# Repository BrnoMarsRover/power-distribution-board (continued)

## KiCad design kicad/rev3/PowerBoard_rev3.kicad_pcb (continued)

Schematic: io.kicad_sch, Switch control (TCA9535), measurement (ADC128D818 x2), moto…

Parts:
C112, C113, C114, C115, C116, C118, C120: 100nF; C_0603_1608Metric_Pad1.08x0.95mm_HandSolder; MPN C0603C104K5RACTU
C117, C119: 1uF/16V; C_0603_1608Metric_Pad1.08x0.95mm_HandSolder; MPN C0603C105K3RACTU
D21: 1N5819HW; D_SOD-123; MPN 1N5819HW-7-F
J36: B2B-XH-A(LF)(SN) (motor switch); JST_XH_B2B-XH-A_1x02_P2.50mm_Vertical; MPN B2B-XH-A(LF)(SN)
J37: B4B-XH-A(LF)(SN) (power button, 2-pole); JST_XH_B4B-XH-A_1x04_P2.50mm_Vertical; MPN B4B-XH-A(LF)(SN)
J38: B2B-XH-A(LF)(SN) (BMS soft-start via E-STOP); JST_XH_B2B-XH-A_1x02_P2.50mm_Vertical; MPN B2B-XH-A(LF)(SN)
R165, R173: 100k; R_0603_1608Metric_Pad0.98x0.95mm_HandSolder; MPN RC0603FR-07100KL
R166, R167, R175: 1k; R_0603_1608Metric_Pad0.98x0.95mm_HandSolder; MPN RC0603FR-071KL
R168, R170, R171, R174: 10k; R_0603_1608Metric_Pad0.98x0.95mm_HandSolder; MPN RC0603FR-0710KL
R169: 1M; R_0603_1608Metric_Pad0.98x0.95mm_HandSolder; MPN RC0603FR-071ML
R172: 330; R_0603_1608Metric_Pad0.98x0.95mm_HandSolder; MPN RC0603FR-07330RL
TP43: MOTOR_KILL; TestPoint_Pad_D1.5mm; MPN none: PCB pad
TP44: GND; TestPoint_Keystone_5015_Micro_Mini; MPN 5015
U17: TCA9535PWR; TSSOP-24_4.4x7.8mm_P0.65mm; MPN TCA9535PWR
U18: SN74LVC1G74DCUT; VSSOP-8_2.3x2mm_P0.5mm; MPN SN74LVC1G74DCUT
U19: SN74LVC1G17DBVR; SOT-23-5; MPN SN74LVC1G17DBVR
U20, U21: ADC128D818; TSSOP-16_4.4x5mm_P0.65mm; MPN ADC128D818CIMTX/NOPB
U22: AQY282S; SO-4_4.4x4.3mm_P2.54mm; MPN AQY282S

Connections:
+3V3: C112.1, C113.1, C116.1, C117.1, C118.1, C119.1, R166.1, R171.1, R174.1, U17.24 (VCC), U18.2 (D), U18.7 (~PRE), U18.8 (VCC), U19.5 (VCC), U20.5 (V+), U21.5 (V+); also elsewhere on the board
/Switch control (TCA9535), measurement (ADC128D818 x2), motor/BTN_SNS: J37.3, R174.2, R175.1
/Switch control (TCA9535), measurement (ADC128D818 x2), motor/SS_A: J37.1, J38.1, U22.3
/Switch control (TCA9535), measurement (ADC128D818 x2), motor/SS_B: J37.2, J38.2, U22.4
BOOST_DIS: U17.18 (P15); also elsewhere on the board
GND: C112.2, C113.2, C114.2, C115.2, C116.2, C117.2, C118.2, C119.2, C120.2, J37.4, R165.2, R168.2, R170.2, R173.2, TP44.1, U17.2 (A1), U17.3 (A2), U17.12 (GND), U17.21 (A0), U18.4 (GND), U19.3 (GND), U20.4 (GND), U20.7 (A0), U20.8 (A1), U20.11 (IN5), U21.4 (GND), U21.8 (A1), U21.9 (IN7), U22.2; also elsewhere on the board
I2C_SCL: U17.22 (SCL), U20.3 (SCL), U21.3 (SCL); also elsewhere on the board
I2C_SDA: U17.23 (SDA), U20.2 (SDA), U21.2 (SDA); also elsewhere on the board
IMON_5: U20.12 (IN4); also elsewhere on the board
IMON_12: U20.13 (IN3); also elsewhere on the board
IMON_24: U20.14 (IN2); also elsewhere on the board
IMON_42C: U20.15 (IN1); also elsewhere on the board
IMON_42D: U20.16 (IN0); also elsewhere on the board
INPG_5: U17.15 (P12); also elsewhere on the board
INPG_12: U17.14 (P11); also elsewhere on the board
INPG_24: U17.13 (P10); also elsewhere on the board
INPG_42C: U17.4 (P00); also elsewhere on the board
INPG_42D: U17.10 (P06); also elsewhere on the board
INP_5: U17.8 (P04); also elsewhere on the board
INP_12: U17.7 (P03); also elsewhere on the board
INP_24: U17.6 (P02); also elsewhere on the board
INP_42C: U17.5 (P01); also elsewhere on the board
INP_42D: U17.11 (P07); also elsewhere on the board
MOTOR_KILL: TP43.1, U18.3 (~Q); also elsewhere on the board
MOTOR_OK: C114.1, D21.1 (K), R167.2, R169.1; also elsewhere on the board
unnamed: C115.1, D21.2 (A), R169.2, U19.2
unnamed: J36.1, R166.2
unnamed: J36.2, R167.1, R168.1
unnamed: R172.2, U22.1
unnamed: R165.1, U17.17 (P14), U18.1 (C)
unnamed: U18.6 (~CLR), U19.4
unnamed: R170.1, R171.2, U21.7 (A0)
PWR_BTN: C120.1, R175.2; also elsewhere on the board
PWR_HOLD: R172.1, R173.1; also elsewhere on the board
VSNS_IN_5: U21.10 (IN6); also elsewhere on the board
VSNS_IN_12: U21.11 (IN5); also elsewhere on the board
VSNS_IN_24: U21.12 (IN4); also elsewhere on the board
VSNS_OUT_5: U21.14 (IN2); also elsewhere on the board
VSNS_OUT_12: U21.15 (IN1); also elsewhere on the board
VSNS_OUT_24: U21.16 (IN0); also elsewhere on the board
VSNS_OUT_42C: U20.9 (IN7); also elsewhere on the board
VSNS_OUT_42D: U20.10 (IN6); also elsewhere on the board
VSNS_OUT_54: U21.13 (IN3); also elsewhere on the board

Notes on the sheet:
It stays off after the switch closes until the ESP32 clocks MOTOR_ARM, which it does only after dropping INP and re-running pre-charge. Power-on also starts latched off. The battery E-STOP is separate (BMS soft-start).
TCA9535 at 0x20 holds INP / INP_G for all five switches, so they keep their state across an ESP32 reset.
Rear-panel motor switch (closed = motors allowed): opening it clears the latch (Q low, /Q high) -> MOTOR_KILL holds the drive group off.
ADC128D818 at 0x1D (A1 = A0 = LOW) and 0x1E (A1 = LOW, A0 = MID). Internal 2.56 V reference (VREF pin open); firmware must select mode 1 (reg 0Bh) or IN7 is not converted. 12 ms per channel.
Soft power: the BMS soft-start loop (through the E-STOP) is closed by button pole 1 or by the AQY282S that the ESP32 holds (PWR_HOLD, GPIO40). Pole 2 reads the button (PWR_BTN, GPIO41, low = on). Button off: the ESP32 asks the Jetson to stow and shut down, then releases PWR_HOLD. A reset or a dead 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
Switch control (TCA9535), measurement (ADC128D818 x2), motor-switch latch
The motor-switch RC (1 M x 100 nF hold-off, diode for a fast clear) goes through a Schmitt buffer into /CLR.

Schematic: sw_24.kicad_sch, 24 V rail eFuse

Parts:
C29: 100nF/100V; C_0603_1608Metric_Pad1.08x0.95mm_HandSolder; MPN CL10B104KC8NNNC
C30: 1uF/100V; C_1206_3216Metric_Pad1.33x1.80mm_HandSolder; MPN GRM31CR72A105KA01L
C31: 10uF/50V; C_1210_3225Metric_Pad1.33x2.70mm_HandSolder; MPN CL32B106KBJNNNE
C32: 270nF/50V; C_1206_3216Metric_Pad1.33x1.80mm_HandSolder; MPN C1206C274K5RACTU
C33, C34, C39: 10nF; C_0603_1608Metric_Pad1.08x0.95mm_HandSolder; MPN CL10B103KB8NNNC
C35: 22uF/10V; C_1206_3216Metric_Pad1.33x1.80mm_HandSolder; MPN CL31B226KPHNNNE
C36: 10uF/25V; C_1206_3216Metric_Pad1.33x1.80mm_HandSolder; MPN CL31A106KAHNNNE
C37, C38: 47uF/35V; CP_Radial_D6.3mm_P2.50mm; MPN EEU-FC1V470
D4: green; LED_0805_2012Metric_Pad1.15x1.40mm_HandSolder; MPN APT2012SGC
D5: SMBJ26A; D_SMB; MPN SMBJ26A
JP3: BYPASS (1.5 mm2 wire bridge); WireBridge_1.5mm2_P5.08mm; MPN none: solid copper wire bridge, fitted 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
Q10, Q11: IPB042N10N3G; TO-263-2; MPN IPB042N10N3GATMA1
Q12: MMBT3904; SOT-23; MPN MMBT3904LT1G
R41: 2m; R_Bourns_CSS2H-2512_Kelvin; MPN CSS2H-2512K-2L00F
R42, R43: 100; R_0603_1608Metric_Pad0.98x0.95mm_HandSolder; MPN RC0603FR-07100RL
R44: 150k; R_0603_1608Metric_Pad0.98x0.95mm_HandSolder; MPN RC0603FR-07150KL
R45: 10k; R_0603_1608Metric_Pad0.98x0.95mm_HandSolder; MPN RC0603FR-0710KL
R46, R47, R51, R56, R57: 100k; R_0603_1608Metric_Pad0.98x0.95mm_HandSolder; MPN RC0603FR-07100KL
R48: 10; R_0603_1608Metric_Pad0.98x0.95mm_HandSolder; MPN RC0603FR-0710RL
R49: 2.2; R_0603_1608Metric_Pad0.98x0.95mm_HandSolder; MPN RC0603FR-072R2L
R50: 330; R_0603_1608Metric_Pad0.98x0.95mm_HandSolder; MPN RC0603FR-07330RL
R52, R54: 9.1k; R_0603_1608Metric_Pad0.98x0.95mm_HandSolder; MPN RC0603FR-079K1L
R53: 10k; R_1206_3216Metric_Pad1.30x1.75mm_HandSolder; MPN RC1206FR-0710KL
R55: 53.6k; R_0603_1608Metric_Pad0.98x0.95mm_HandSolder; MPN RC0603FR-0753K6L
R58: 8.2k; R_0603_1608Metric_Pad0.98x0.95mm_HandSolder; MPN RC0603FR-078K2L
TP10: FLT_24; TestPoint_Pad_D1.5mm; MPN none: PCB pad
TP11: GATE; TestPoint_Pad_D1.5mm; MPN none: PCB pad
TP12: OUT24; TestPoint_Pad_D1.5mm; MPN none: PCB pad
TP13: IMON_24; TestPoint_Pad_D1.5mm; MPN none: PCB pad
U4: TPS48111-Q1; TI_DGX0019A_VSSOP-19; MPN TPS48111LQDGXRQ1

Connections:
/24 V rail eFuse/DRN: JP3.1 (A), Q10.2 (D), Q11.2 (D), R41.4
FLT_24: TP10.1, U4.4 (FLT_T), U4.5 (FLT_I); also elsewhere on the board
GND: C29.2, C30.2, C32.2, C33.2, C34.2, C35.2, C36.2, C37.2, C38.2, C39.2, D4.1 (K), D5.2 (A), Q12.2 (E), R45.2, R46.2, R47.2, R52.2, R54.2, R55.2, R56.2, R58.2, U4.6 (GND); also elsewhere on the board
IMON_24: C34.1, R54.1, TP13.1, U4.7 (IMON); also elsewhere on the board
INPG_24: R47.1, U4.2 (INP_G); also elsewhere on the board
INP_24: R46.1, U4.3 (INP); also elsewhere on the board
unnamed: C32.1, R50.2
unnamed: D4.2 (A), R53.2
unnamed: Q10.1 (G), R49.2
unnamed: Q11.1 (G), R50.1, U4.11 (G)
unnamed: Q12.1 (B), Q12.3 (C), U4.10 (DIODE)
unnamed: R41.2, R42.1
unnamed: C31.1, U4.12 (BST)
unnamed: R42.2, U4.18 (CS+)
unnamed: R41.3, U4.17 (CS-), U4.19 (ISCP)
unnamed: R44.2, R45.1, U4.1 (EN/UVLO)
unnamed: R55.1, U4.8 (IWRN)
unnamed: R48.2, R49.1, TP11.1, U4.14 (PD)
unnamed: R48.1, U4.15 (PU)
unnamed: C35.1, C36.1, R56.1, U4.9 (TMR)
unnamed: C29.1, C30.1, R43.2, U4.20 (VS)
OUT24: C31.2, JP3.2 (B), Q10.3 (S), Q11.3 (S), R51.1, R53.1, TP12.1, U4.13 (SRC); also elsewhere on the board
VIN24: C37.1, C38.1, D5.1 (K), R41.1, R43.1, R44.1, R57.1; also elsewhere on the board
VSNS_IN_24: C39.1, R57.2, R58.1; also elsewhere on the board
VSNS_OUT_24: C33.1, R51.2, R52.1; also elsewhere on the board

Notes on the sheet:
TPS48111-Q1 + 1 x IPB042N10N3G main + 1 pre-charge. Values from docs/rev3/rails.md (trip 11.1 A after 506 ms, latch-off; short-circuit trip disabled).
Kelvin-route CS+ / CS- / ISCP from the R_SNS pads. Place C_ISCP right at the pins.
24 V rail eFuse
Power-on: OFF in hardware. Q_T (MMBT3904) must sit against the main FET: remote temperature sense.

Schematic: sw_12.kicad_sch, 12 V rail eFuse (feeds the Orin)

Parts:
C40: 100nF/100V; C_0603_1608Metric_Pad1.08x0.95mm_HandSolder; MPN CL10B104KC8NNNC
C41: 1uF/100V; C_1206_3216Metric_Pad1.33x1.80mm_HandSolder; MPN GRM31CR72A105KA01L
C42: 10uF/50V; C_1210_3225Metric_Pad1.33x2.70mm_HandSolder; MPN CL32B106KBJNNNE
C43: 150nF/50V; C_1206_3216Metric_Pad1.33x1.80mm_HandSolder; MPN C1206C154K5RACTU
C44, C45, C50: 10nF; C_0603_1608Metric_Pad1.08x0.95mm_HandSolder; MPN CL10B103KB8NNNC
C46: 22uF/10V; C_1206_3216Metric_Pad1.33x1.80mm_HandSolder; MPN CL31B226KPHNNNE
C47: 10uF/25V; C_1206_3216Metric_Pad1.33x1.80mm_HandSolder; MPN CL31A106KAHNNNE
C48, C49: 47uF/35V; CP_Radial_D6.3mm_P2.50mm; MPN EEU-FC1V470
D6: green; LED_0805_2012Metric_Pad1.15x1.40mm_HandSolder; MPN APT2012SGC
D7: SMBJ13A; D_SMB; MPN SMBJ13A
JP4: BYPASS (1.5 mm2 wire bridge); WireBridge_1.5mm2_P5.08mm; MPN none: solid copper wire bridge, fitted 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
Q13, Q14: IPB042N10N3G; TO-263-2; MPN IPB042N10N3GATMA1
Q15: MMBT3904; SOT-23; MPN MMBT3904LT1G
R59: 2m; R_Bourns_CSS2H-2512_Kelvin; MPN CSS2H-2512K-2L00F
R60, R61: 100; R_0603_1608Metric_Pad0.98x0.95mm_HandSolder; MPN RC0603FR-07100RL
R62: 68k; R_0603_1608Metric_Pad0.98x0.95mm_HandSolder; MPN RC0603FR-0768KL
R63: 10k; R_0603_1608Metric_Pad0.98x0.95mm_HandSolder; MPN RC0603FR-0710KL
R64, R65, R69, R74, R75: 100k; R_0603_1608Metric_Pad0.98x0.95mm_HandSolder; MPN RC0603FR-07100KL
R66: 10; R_0603_1608Metric_Pad0.98x0.95mm_HandSolder; MPN RC0603FR-0710RL
R67: 2.2; R_0603_1608Metric_Pad0.98x0.95mm_HandSolder; MPN RC0603FR-072R2L
R68: 330; R_0603_1608Metric_Pad0.98x0.95mm_HandSolder; MPN RC0603FR-07330RL
R70: 20k; R_0603_1608Metric_Pad0.98x0.95mm_HandSolder; MPN RC0603FR-0720KL
R71: 4.7k; R_0603_1608Metric_Pad0.98x0.95mm_HandSolder; MPN RC0603FR-074K7L
R72: 9.1k; R_0603_1608Metric_Pad0.98x0.95mm_HandSolder; MPN RC0603FR-079K1L
R73: 53.6k; R_0603_1608Metric_Pad0.98x0.95mm_HandSolder; MPN RC0603FR-0753K6L
R76: 18k; R_0603_1608Metric_Pad0.98x0.95mm_HandSolder; MPN RC0603FR-0718KL
TP14: FLT_12; TestPoint_Pad_D1.5mm; MPN none: PCB pad
TP15: GATE; TestPoint_Pad_D1.5mm; MPN none: PCB pad
TP16: OUT12; TestPoint_Pad_D1.5mm; MPN none: PCB pad
TP17: IMON_12; TestPoint_Pad_D1.5mm; MPN none: PCB pad
U5: TPS48111-Q1; TI_DGX0019A_VSSOP-19; MPN TPS48111LQDGXRQ1

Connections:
/12 V rail eFuse (feeds the Orin)/DRN: JP4.1 (A), Q13.2 (D), Q14.2 (D), R59.4
FLT_12: TP14.1, U5.4 (FLT_T), U5.5 (FLT_I); also elsewhere on the board
GND: C40.2, C41.2, C43.2, C44.2, C45.2, C46.2, C47.2, C48.2, C49.2, C50.2, D6.1 (K), D7.2 (A), Q15.2 (E), R63.2, R64.2, R65.2, R70.2, R72.2, R73.2, R74.2, R76.2, U5.6 (GND); also elsewhere on the board
IMON_12: C45.1, R72.1, TP17.1, U5.7 (IMON); also elsewhere on the board
INPG_12: R65.1, U5.2 (INP_G); also elsewhere on the board
INP_12: R64.1, U5.3 (INP); also elsewhere on the board
unnamed: C43.1, R68.2
unnamed: D6.2 (A), R71.2
unnamed: Q13.1 (G), R67.2
unnamed: Q14.1 (G), R68.1, U5.11 (G)
unnamed: Q15.1 (B), Q15.3 (C), U5.10 (DIODE)
unnamed: R59.2, R60.1
unnamed: C42.1, U5.12 (BST)
unnamed: R60.2, U5.18 (CS+)
unnamed: R59.3, U5.17 (CS-), U5.19 (ISCP)
unnamed: R62.2, R63.1, U5.1 (EN/UVLO)
unnamed: R73.1, U5.8 (IWRN)
unnamed: R66.2, R67.1, TP15.1, U5.14 (PD)
unnamed: R66.1, U5.15 (PU)
unnamed: C46.1, C47.1, R74.1, U5.9 (TMR)
unnamed: C40.1, C41.1, R61.2, U5.20 (VS)
OUT12: C42.2, JP4.2 (B), Q13.3 (S), Q14.3 (S), R69.1, R71.1, TP16.1, U5.13 (SRC); also elsewhere on the board
VIN12: C48.1, C49.1, D7.1 (K), R59.1, R61.1, R62.1, R75.1; also elsewhere on the board
VSNS_IN_12: C50.1, R75.2, R76.1; also elsewhere on the board
VSNS_OUT_12: C44.1, R69.2, R70.1; also elsewhere on the board

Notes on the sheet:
Kelvin-route CS+ / CS- / ISCP from the R_SNS pads. Place C_ISCP right at the pins.
TPS48111-Q1 + 1 x IPB042N10N3G main + 1 pre-charge. Values from docs/rev3/rails.md (trip 11.1 A after 506 ms, latch-off; short-circuit trip disabled).
12 V rail eFuse (feeds the Orin)
Power-on: OFF in hardware; the ESP32 turns it on at boot (rails.md, power-on sequence). Q_T (MMBT3904) must sit against the main FET: remote temperature sense.

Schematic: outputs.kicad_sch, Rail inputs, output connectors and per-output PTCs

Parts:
F1, F2, F3, F4, F5, F6: SMD2920B300TF/30; Fuse_2920_7451Metric_Pad2.10x5.45mm_HandSolder; MPN SMD2920B300TF/30
F7, F8, F9, F10, F11, F12: MF-LSMF300/16X-2; Fuse_2920_7451Metric_Pad2.10x5.45mm_HandSolder; MPN MF-LSMF300/16X-2
F13, F14, F15, F16, F17, F18: MF-LSMF300X-2; Fuse_2920_7451Metric_Pad2.10x5.45mm_HandSolder; MPN MF-LSMF300X-2
F19: 0154003.DRT (3 A slow-blow, clip holder); Fuseholder_Littelfuse_Nano2_154x; MPN 0154003.DRT
J5: Deans T male (24 V in); DEANS-T; MPN none: Deans T, bought outside TME / Mou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
J6: XT60PT-M (12 V in); AMASS_XT60-M_1x02_P7.20mm_Vertical; MPN XT60PT-M
J7: XT30UPB-M (5 V in); AMASS_XT30UPB-M_1x02_P5.0mm_Vertical; MPN XT30UPB-M
J8, J9, J10, J11, J12: XT90PB-F; MPN XT90PB-F
J13: B2B-XH-A(LF)(SN) (54 V to Zyxel); JST_XH_B2B-XH-A_1x02_P2.50mm_Vertical; MPN B2B-XH-A(LF)(SN)
J14, J15, J16, J17, J18, J19: Deans T female; DEANS-T; MPN none: Deans T, bought outside TME / Mou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
J20, J21, J22, J23, J24, J25: XT60PT-F; AMASS_XT60-F_1x02_P7.20mm_Vertical; MPN XT60PT-F
J26, J27, J28, J29, J30, J31: XT30UPB-F; AMASS_XT30UPB-F_1x02_P5.0mm_Vertical; MPN XT30UPB-F

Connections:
/Rail inputs, output connectors and per-output PTCs/O5_1: F13.2, J26.2 (+)
/Rail inputs, output connectors and per-output PTCs/O5_2: F14.2, J27.2 (+)
/Rail inputs, output connectors and per-output PTCs/O5_3: F15.2, J28.2 (+)
/Rail inputs, output connectors and per-output PTCs/O5_4: F16.2, J29.2 (+)
/Rail inputs, output connectors and per-output PTCs/O5_5: F17.2, J30.2 (+)
/Rail inputs, output connectors and per-output PTCs/O5_6: F18.2, J31.2 (+)
/Rail inputs, output connectors and per-output PTCs/O12_1: F7.2, J20.2 (+)
/Rail inputs, output connectors and per-output PTCs/O12_2: F8.2, J21.2 (+)
/Rail inputs, output connectors and per-output PTCs/O12_3: F9.2, J22.2 (+)
/Rail inputs, output connectors and per-output PTCs/O12_4: F10.2, J23.2 (+)
/Rail inputs, output connectors and per-output PTCs/O12_5: F11.2, J24.2 (+)
/Rail inputs, output connectors and per-output PTCs/O12_6: F12.2, J25.2 (+)
/Rail inputs, output connectors and per-output PTCs/O24_1: F1.2, J14.2 (+)
/Rail inputs, output connectors and per-output PTCs/O24_2: F2.2, J15.2 (+)
/Rail inputs, output connectors and per-output PTCs/O24_3: F3.2, J16.2 (+)
/Rail inputs, output connectors and per-output PTCs/O24_4: F4.2, J17.2 (+)
/Rail inputs, output connectors and per-output PTCs/O24_5: F5.2, J18.2 (+)
/Rail inputs, output connectors and per-output PTCs/O24_6: F6.2, J19.2 (+)
/Rail inputs, output connectors and per-output PTCs/O54_1: F19.2, J13.1
GND: J5.1 (-), J6.1 (-), J7.1 (-), J8.2, J9.2, J10.2, J11.2, J12.2, J13.2, J14.1 (-), J15.1 (-), J16.1 (-), J17.1 (-), J18.1 (-), J19.1 (-), J20.1 (-), J21.1 (-), J22.1 (-), J23.1 (-), J24.1 (-), J25.1 (-), J26.1 (-), J27.1 (-), J28.1 (-), J29.1 (-), J30.1 (-), J31.1 (-); also elsewhere on the board
OUT5: F13.1, F14.1, F15.1, F16.1, F17.1, F18.1; also elsewhere on the board
OUT12: F7.1, F8.1, F9.1, F10.1, F11.1, F12.1; also elsewhere on the board
OUT24: F1.1, F2.1, F3.1, F4.1, F5.1, F6.1; also elsewhere on the board
OUT42C: J11.1, J12.1; also elsewhere on the board
OUT42D: J8.1, J9.1, J10.1; also elsewhere on the board
OUT54: F19.1; also elsewhere on the board
VIN5: J7.2 (+); also elsewhere on the board
VIN12: J6.2 (+); also elsewhere on the board
VIN24: J5.2 (+); also elsewhere on the board

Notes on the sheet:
OUT42D = drive group (3 x XT90, two EPOS4 50/5 per XT90). OUT42C = 2 converter feeds; one is Y-split in the harness for the third converter.
Male connectors are inputs (the cable side is the source), female are outputs. Pin 1 = +.
PTC per 24 / 12 / 5 V output: 3 A hold. Device cables must carry the PTC trip current (AWG 20 or heavier).
Rail inputs, output connectors and per-output PTCs
Check every connector footprint's pin 1 against the housing's + marking before ordering.

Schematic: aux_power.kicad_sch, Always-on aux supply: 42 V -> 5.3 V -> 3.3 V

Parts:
C93, C94: 2.2uF/100V; C_1210_3225Metric_Pad1.33x2.70mm_HandSolder; MPN GRM32ER72A225KA35L
C95: 10nF/25V; C_0603_1608Metric_Pad1.08x0.95mm_HandSolder; MPN CL10B103KB8NNNC
C96: 1uF/16V; C_0603_1608Metric_Pad1.08x0.95mm_HandSolder; MPN C0603C105K3RACTU
C97, C98, C99, C102: 22uF/25V; C_1206_3216Metric_Pad1.33x1.80mm_HandSolder; MPN CL31A226KAHNNNE
C100: 3.3nF/50V; C_0603_1608Metric_Pad1.08x0.95mm_HandSolder; MPN CL10B332KB8NNNC
C101: 100nF/16V; C_0603_1608Metric_Pad1.08x0.95mm_HandSolder; MPN C0603C104K5RACTU
C103: 10uF/10V; C_0805_2012Metric_Pad1.18x1.45mm_HandSolder; MPN CL21B106KOQNNNE
C104: 100nF; C_0603_1608Metric_Pad1.08x0.95mm_HandSolder; MPN C0603C104K5RACTU
D16, D17: SS34; D_SMA; MPN SS34-E3/57T
L2: 33uH; L_Bourns_SRR1260; MPN SRR1260-330M
R136: 150k; R_0805_2012Metric_Pad1.20x1.40mm_HandSolder; MPN RC0805FR-07150KL
R137, R139: 100k; R_0805_2012Metric_Pad1.20x1.40mm_HandSolder; MPN RC0805FR-07100KL
R138: 6.8k; R_0603_1608Metric_Pad0.98x0.95mm_HandSolder; MPN RC0603FR-076K8L
R140: 33.2k; R_0603_1608Metric_Pad0.98x0.95mm_HandSolder; MPN RC0603FR-0733K2L
R141: 10k; R_0603_1608Metric_Pad0.98x0.95mm_HandSolder; MPN RC0603FR-0710KL
TP31: VCC; TestPoint_Pad_D1.5mm; MPN none: PCB pad
TP32: SW; TestPoint_Pad_D1.5mm; MPN none: PCB pad
TP33: GND; TestPoint_Keystone_5015_Micro_Mini; MPN 5015
TP34: +5V3_AUX; TestPoint_Pad_D1.5mm; MPN none: PCB pad
TP35: +5V_LOGIC; TestPoint_Pad_D1.5mm; MPN none: PCB pad
TP36: +3V3; TestPoint_Pad_D1.5mm; MPN none: PCB pad
U11: LM5017MR/NOPB; SOIC-8-1EP_3.9x4.9mm_P1.27mm_EP2.41x3.3mm; MPN LM5017MR/NOPB
U12: AP7361C-33ER; SOT-223-3_TabPin2; MPN AP7361C-33ER-13

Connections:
+3V3: C103.1, C104.1, TP36.1, U12.2 (VO); also elsewhere on the board
+5V3_AUX: C97.1, C98.1, C99.1, C100.1, D16.2 (A), L2.2, R140.1, TP34.1
+5V_LOGIC: C102.1, D16.1 (K), D17.1 (K), TP35.1, U12.3 (VI); also elsewhere on the board
BUS42: C93.1, C94.1, R136.1, R137.1, U11.2 (VIN); also elsewhere on the board
GND: C93.2, C94.2, C96.2, C97.2, C98.2, C99.2, C102.2, C103.2, C104.2, R138.2, R141.2, TP33.1, U11.1 (RTN), U11.9 (EP), U12.1 (GND); also elsewhere on the board
unnamed: C100.2, C101.1, R139.2
unnamed: C95.1, U11.7 (BST)
unnamed: C101.2, R140.2, R141.1, U11.5 (FB)
unnamed: R136.2, U11.4 (RON)
unnamed: C95.2, L2.1, R139.1, TP32.1, U11.8 (SW)
unnamed: R137.2, R138.1, U11.3 (UVLO)
unnamed: C96.1, TP31.1, U11.6 (VCC)
VBUS_USB: D17.2 (A); also elsewhere on the board

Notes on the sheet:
Bring-up test: battery only, USB unplugged -> +5V3_AUX, +5V_LOGIC and +3V3 present, ESP32 boots.
Always-on aux supply: 42 V -> 5.3 V -> 3.3 V
Constant on-time buck: RON from VIN sets ~400 kHz; Rr / Cr / Cac inject the ripple FB needs (TI 'Type 3', datasheet 7.3.11).
LM5017 runs from the battery bus before any switch, so logic power never depends on USB (rule R1).

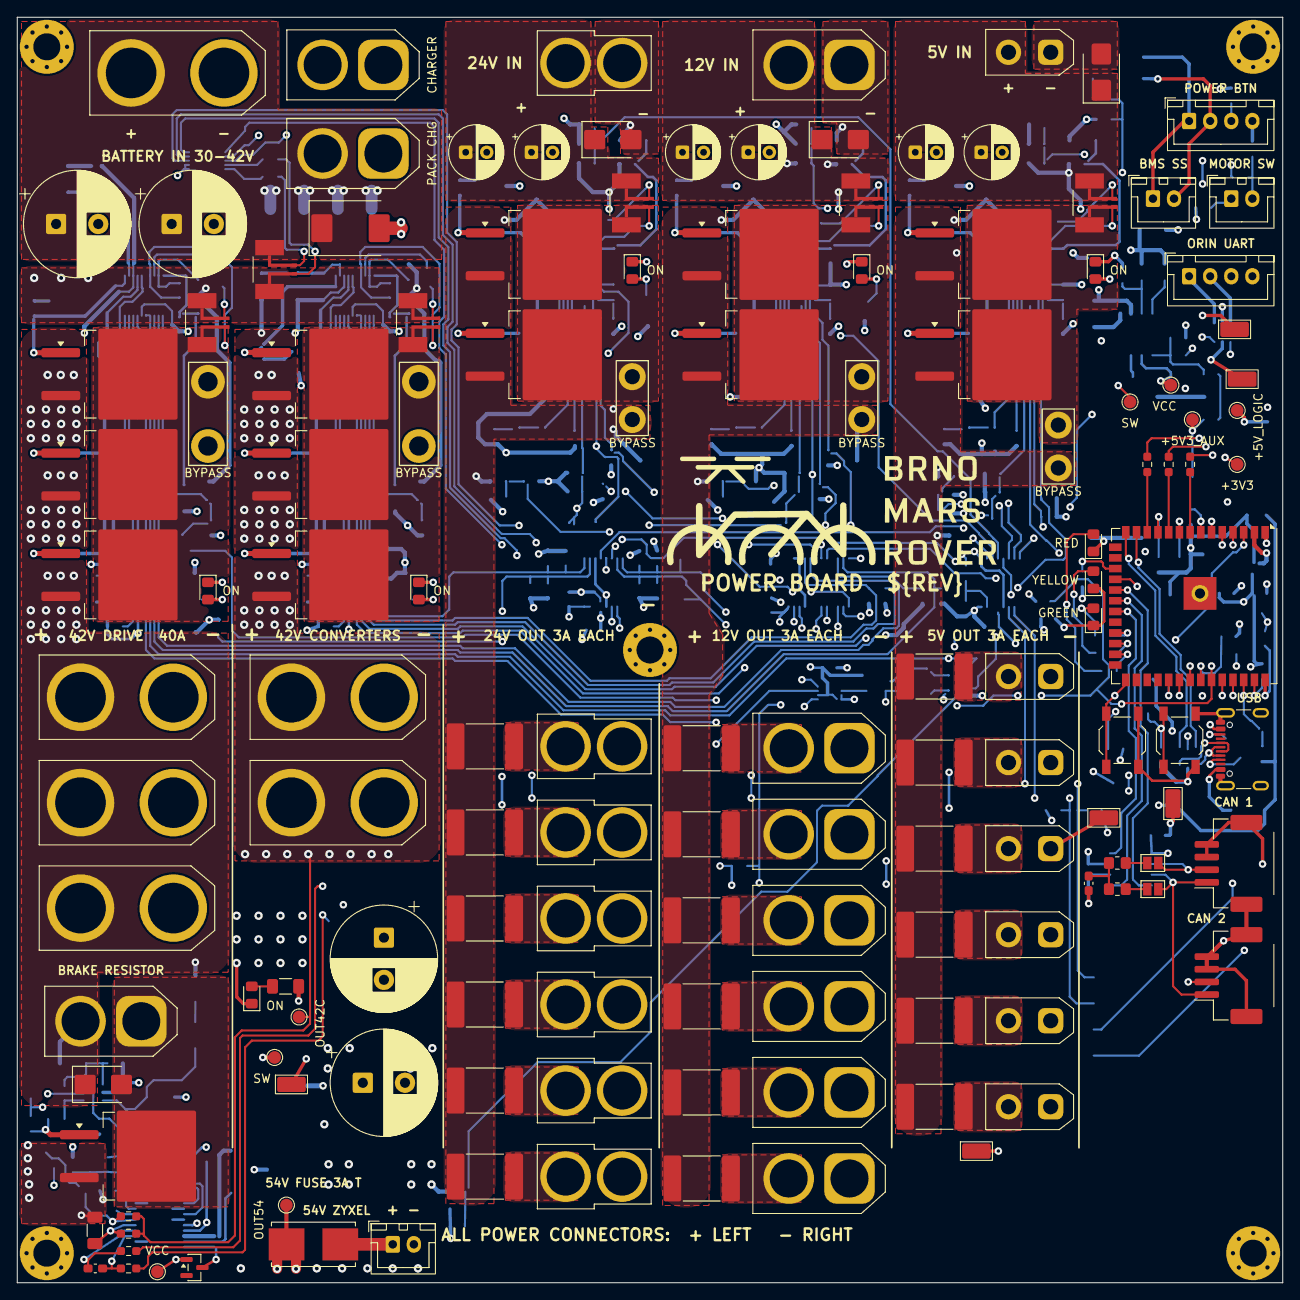
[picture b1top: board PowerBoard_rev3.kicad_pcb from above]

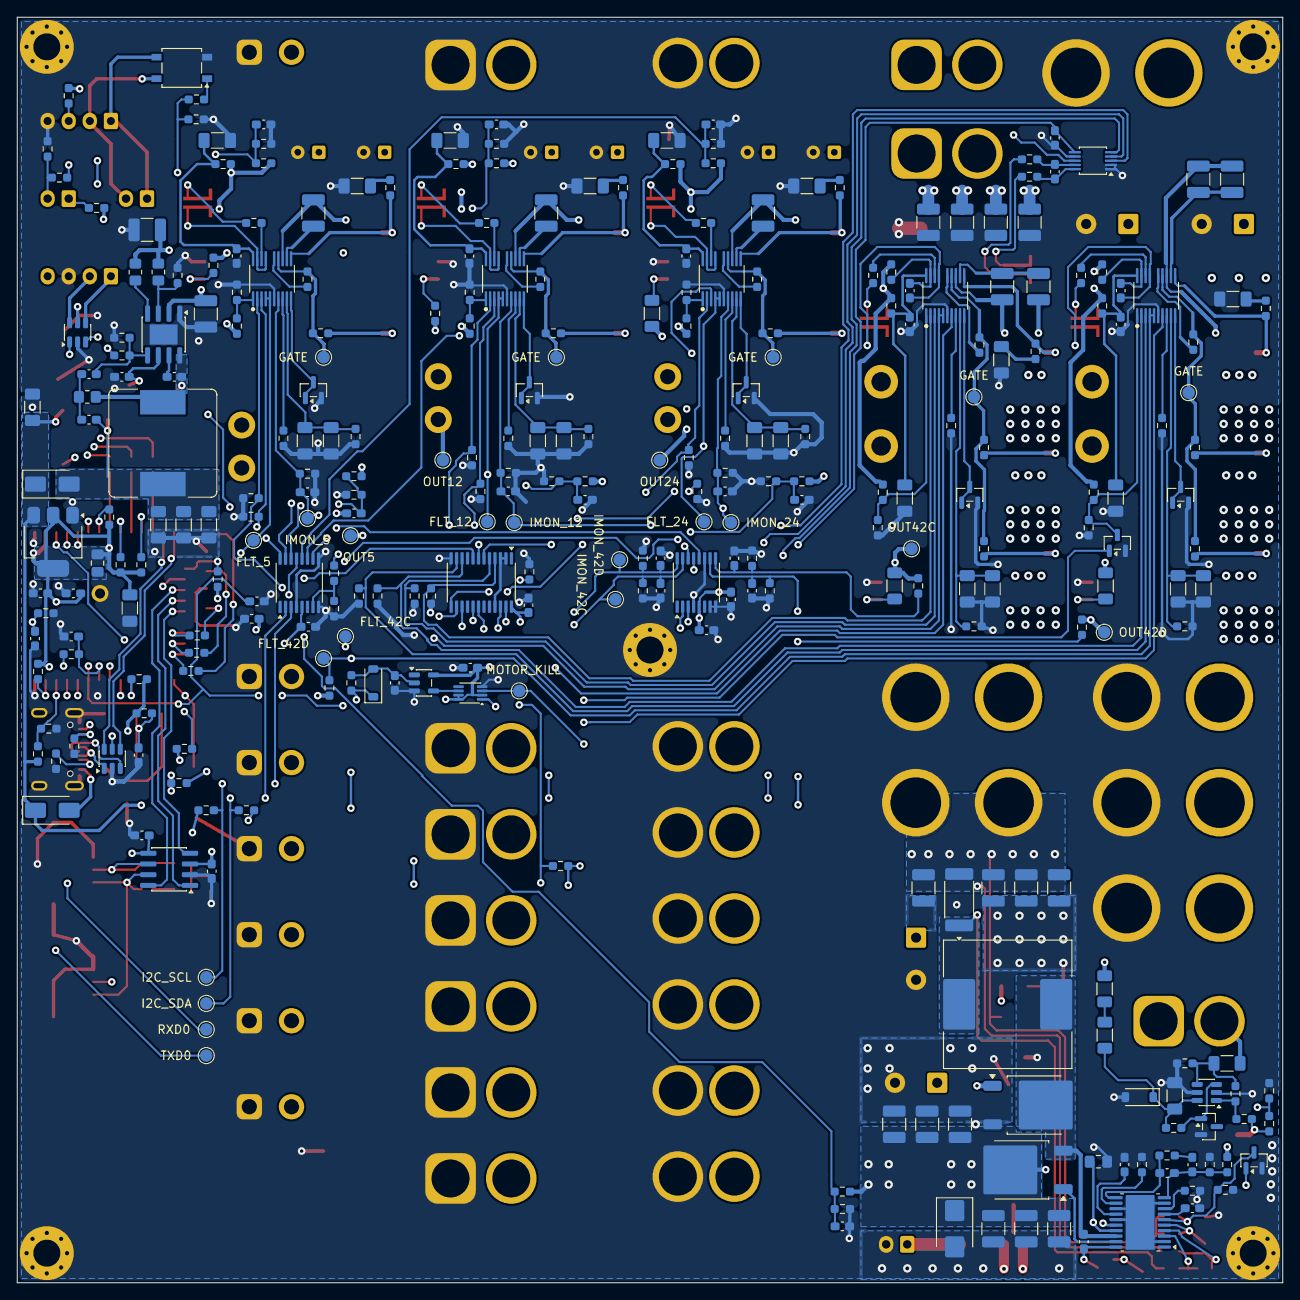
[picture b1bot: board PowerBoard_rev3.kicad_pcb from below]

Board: 4 copper layers, 150.0 x 150.0 mm, 447 parts (302 on the bottom side), 239 nets.

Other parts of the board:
H1, H2, H3, H4, H5: M3; MountingHole_3.2mm_M3_Pad_Via
LOGO: BMR_Logo

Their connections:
GND: H1.1, H2.1, H3.1, H4.1, H5.1; also elsewhere on the board

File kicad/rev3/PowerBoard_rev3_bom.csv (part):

"MPN","Value","Footprint","Qty","References"
"5015","GND","TestPoint:TestPoint_Keystone_5015_Micro_Mini","6","TP1,TP29,TP33,TP41,TP42,TP44"
"0154003.DRT","0154003.DRT (3 A slow-blow, clip holder)","Fuse:Fuseholder_Littelfuse_Nano2_154x","1","F19"
"1N5819HW-7-F","1N5819HW","Diode_SMD:D_SOD-123","1","D21"
"2N7002LT1G","2N7002","Package_TO_SOT_SMD:SOT-23","2","Q1,Q25"
"502585-0470","CAN 1 (Molex CLIK-Mate 502585-0470),CAN 2 (Molex CLIK-Mate 502585-0470)","Connector_Molex:Molex_CLIK-Mate_502585-0470_1x04-1MP_P1.50mm_Horizontal","2","J34,J35"
"ADC128D818CIMTX/NOPB","ADC128D818","Package_SO:TSSOP-16_4.4x5mm_P0.65mm","2","U20,U21"
"APT2012SGC","green","LED_SMD:LED_0805_2012Metric_Pad1.15x1.40mm_HandSolder","7","D2-D4,D6,D8,D15,D18"
"APT2012SURCK","red","LED_SMD:LED_0805_2012Metric_Pad1.15x1.40mm_HandSolder","1","D20"
"APT2012SYCK","yellow","LED_SMD:LED_0805_2012Metric_Pad1.15x1.40mm_HandSolder","1","D19"
"AP7361C-33ER-13","AP7361C-33ER","Package_TO_SOT_SMD:SOT-223-3_TabPin2","1","U12"
"AQY282S","AQY282S","Package_SO:SO-4_4.4x4.3mm_P2.54mm","1","U22"
"B2B-XH-A(LF)(SN)","B2B-XH-A(LF)(SN) (54 V to Zyxel),B2B-XH-A(LF)(SN) (BMS soft-start via E-STOP),B2B-XH-A(LF)(SN) (motor switch)","Connector_JST:JST_XH_B2B-XH-A_1x02_P2.50mm_Vertical","3","J13,J36,J38"
"B4B-XH-A(LF)(SN)","B4B-XH-A(LF)(SN) (host UART to Orin),B4B-XH-A(LF)(SN) (power button, 2-pole)","Connector_JST:JST_XH_B4B-XH-A_1x04_P2.50mm_Vertical","2","J33,J37"
"BAS21-7-F","BAS21","Package_TO_SOT_SMD:SOT-23","1","D13"
"C0603C104K5RACTU","100nF,100nF/16V,100nF/25V","Capacitor_SMD:C_0603_1608Metric_Pad1.08x0.95mm_HandSolder","17","C7,C8,C78,C80,C101,C104,C106,C108-C110,C112-C116,C118,C120"
"C0603C105K3RACTU","1uF,1uF/16V","Capacitor_SMD:C_0603_1608Metric_Pad1.08x0.95mm_HandSolder","4","C96,C107,C117,C119"
"C0603C102J5GACTU","1nF","Capacitor_SMD:C_0603_1608Metric_Pad1.08x0.95mm_HandSolder","3","C9,C19,C77"
"C0603C820J5GACTU","82pF","Capacitor_SMD:C_0603_1608Metric_Pad1.08x0.95mm_HandSolder","1","C82"
"C1206C105K1RACTU","1uF/100V","Capacitor_SMD:C_1206_3216Metric_Pad1.33x1.80mm_HandSolder","1","C76"
"C1206C154K5RACTU","150nF/50V","Capacitor_SMD:C_1206_3216Metric_Pad1.33x1.80mm_HandSolder","1","C43"
"C1206C274K5RACTU","270nF/50V","Capacitor_SMD:C_1206_3216Metric_Pad1.33x1.80mm_HandSolder","1","C32"
"C1206C474K1RACTU","470nF/100V","Capacitor_SMD:C_1206_3216Metric_Pad1.33x1.80mm_HandSolder","1","C24"
"C1206C683K5RACTU","68nF/50V","Capacitor_SMD:C_1206_3216Metric_Pad1.33x1.80mm_HandSolder","1","C54"
"C1210C225K1RACTU","2.2uF/100V","Capacitor_SMD:C_1210_3225Metric_Pad1.33x2.70mm_HandSolder","10","C72-C75,C84-C89"
"C3216X7R2A684K160AA","680nF/100V","Capacitor_SMD:C_1206_3216Metric_Pad1.33x1.80mm_HandSolder","1","C14"
"CL10B103KB8NNNC","10nF,10nF/25V","Capacitor_SMD:C_0603_1608Metric_Pad1.08x0.95mm_HandSolder","15","C15,C16,C25,C26,C33,C34,C39,C44,C45,C50,C55,C56,C61,C92,C95"
"CL10B104KC8NNNC","100nF/100V","Capacitor_SMD:C_0603_1608Metric_Pad1.08x0.95mm_HandSolder","5","C10,C20,C29,C40,C51"
"CL10B153KB8NNNC","15nF","Capacitor_SMD:C_0603_1608Metric_Pad1.08x0.95mm_HandSolder","1","C83"
"CL10B332KB8NNNC","3.3nF/50V","Capacitor_SMD:C_0603_1608Metric_Pad1.08x0.95mm_HandSolder","1","C100"
"CL10B472KB8NNNC","4.7nF/50V","Capacitor_SMD:C_0603_1608Metric_Pad1.08x0.95mm_HandSolder","1","C111"
"CL10B474KA8NNNC","470nF","Capacitor_SMD:C_0603_1608Metric_Pad1.08x0.95mm_HandSolder","1","C81"
"CL21B106KOQNNNE","10uF/10V","Capacitor_SMD:C_0805_2012Metric_Pad1.18x1.45mm_HandSolder","1","C103"
"CL21B475KOFNNNE","4.7uF/16V","Capacitor_SMD:C_0805_2012Metric_Pad1.18x1.45mm_HandSolder","1","C79"
"CL31A106KAHNNNE","10uF/25V","Capacitor_SMD:C_1206_3216Metric_Pad1.33x1.80mm_HandSolder","5","C28,C36,C47,C58,C71"
"CL31A226KAHNNNE","22uF/25V","Capacitor_SMD:C_1206_3216Metric_Pad1.33x1.80mm_HandSolder","4","C97-C99,C102"
"CL31A476MQHNNNE","47uF/6.3V","Capacitor_SMD:C_1206_3216Metric_Pad1.33x1.80mm_HandSolder","1","C17"
"CL31B226KPHNNNE","22uF/10V","Capacitor_SMD:C_1206_3216Metric_Pad1.33x1.80mm_HandSolder","6","C18,C27,C35,C46,C57,C105"
"CL32B106KBJNNNE","10uF/50V","Capacitor_SMD:C_1210_3225Metric_Pad1.33x2.70mm_HandSolder","7","C12,C13,C22,C23,C31,C42,C53"
"CSS2H-2512K-2L00F","2m,2m 5W","PowerBoard_rev3:R_Bourns_CSS2H-2512_Kelvin","3","R1,R41,R59"
"CSS2H-2512R-L500F","0.5m","PowerBoard_rev3:R_Bourns_CSS2H-2512_Kelvin","1","R5"
"CSS2H-2512R-1L00F","1m","PowerBoard_rev3:R_Bourns_CSS2H-2512_Kelvin","2","R23,R77"
"EEU-FC1V470","47uF/35V","Capacitor_THT:CP_Radial_D6.3mm_P2.50mm","6","C37,C38,C48,C49,C59,C60"
"EEU-FC2A101","100uF/100V","Capacitor_THT:CP_Radial_D12.5mm_P5.00mm","4","C1,C2,C90,C91"
"ERJ-3RQF3R0V","3","Resistor_SMD:R_0603_1608Metric_Pad0.98x0.95mm_HandSolder","1","R122"
"ERJ-6ENF60R4V","60.4","Resistor_SMD:R_0805_2012Metric_Pad1.20x1.40mm_HandSolder","2","R163,R164"
"ESP32-S3-WROOM-1U-N8","ESP32-S3-WROOM-1U-N8","PowerBoard_rev3:ESP32-S3-WROOM-1U_HandSolder","1","U13"
"FDD86102","FDD86102","Package_TO_SOT_SMD:TO-252-2","2","Q23,Q24"
"GRM31CR72A105KA01L","1uF/100V","Capacitor_SMD:C_1206_3216Metric_Pad1.33x1.80mm_HandSolder","5","C11,C21,C30,C41,C52"
"GRM32ER72A225KA35L","2.2uF/100V","Capacitor_SMD:C_1210_3225Metric_Pad1.33x2.70mm_HandSolder","6","C3-C6,C93,C94"
"INA228AIDGSR","INA228AIDGSR","Package_SO:TSSOP-10_3x3mm_P0.5mm","1","U1"
"IPB042N10N3GATMA1","IPB042N10N3G","Package_TO_SOT_SMD:TO-263-2","13","Q2-Q4,Q6-Q8,Q10,Q11,Q13,Q14,Q16,Q17,Q22"
"LM5017MR/NOPB","LM5017MR/NOPB","Package_SO:SOIC-8-1EP_3.9x4.9mm_P1.27mm_EP2.41x3.3mm","1","U11"
"LM5122MHX/NOPB","LM5122MH","Package_SO:HTSSOP-20-1EP_4.4x6.5mm_P0.65mm_EP3.4x6.5mm_Mask2.96x2.96mm","1","U10"
"LM4040B25IDBZR","LM4040 2.5V","Package_TO_SOT_SMD:SOT-23","1","U9"
"MF-LSMF300/16X-2","MF-LSMF300/16X-2","Fuse:Fuse_2920_7451Metric_Pad2.10x5.45mm_HandSolder","6","F7-F12"
"MF-LSMF300X-2","MF-LSMF300X-2","Fuse:Fuse_2920_7451Metric_Pad2.10x5.45mm_HandSolder","6","F13-F18"
"MMBT3904LT1G","MMBT3904","Package_TO_SOT_SMD:SOT-23","5","Q5,Q9,Q12,Q15,Q18"
"MMSZ5242BT1G","12V","Diode_SMD:D_SOD-123","1","D11"
"MSS1583-223MED","22uH 10.4A","Inductor_SMD:L_Coilcraft_MSS1583-XXX","1","L1"
"NCP18XH103F03RB","10k NTC","Resistor_SMD:R_0603_1608Metric_Pad0.98x0.95mm_HandSolder","1","TH1"
"none: Deans T, bought outside TME / Mouser (sourcing exception)","Deans T female,Deans T male (24 V in)","PowerBoard_rev3:DEANS-T","7","J5,J14-J19"
"none: PCB pad","+3V3,+5V3_AUX,+5V_LOGIC,FLT_12,FLT_24,FLT_42C,FLT_42D,FLT_5,GATE,I2C_SCL,I2C_SDA,IMON_12,IMON_24,IMON_42C,IMON_42D,IMON_5,MOTOR_KILL,OUT12,OUT24,OUT42C,OUT42D,OUT5,OUT54,RXD0,SW,TXD0,VCC","TestPoint:TestPoint_Pad_D1.5mm","34","TP2-TP21,TP26-TP28,TP30-TP32,TP34-TP40,TP43"
"none: PCB solder jumper","TERM_H,TERM_L","Jumper:SolderJumper-2_P1.3mm_Open_Pad1.0x1.5mm","2","JP7,JP8"
"none: solid copper wire bridge, fitted only in an emergency","BYPASS (2.5 mm2 wire bridge)","PowerBoard_rev3:WireBridge_2.5mm2_P7.62mm","2","JP1,JP2"
"none: solid copper wire bridge, fitted only in an emergency","BYPASS (1.5 mm2 wire bridge)","PowerBoard_rev3:WireBridge_1.5mm2_P5.08mm","3","JP3-JP5"
"RC0603FR-071KL","1k","Resistor_SMD:R_0603_1608Metric_Pad0.98x0.95mm_HandSolder","9","R151-R153,R160-R162,R166,R167,R175"
"RC0603FR-071ML","1M","Resistor_SMD:R_0603_1608Metric_Pad0.98x0.95mm_HandSolder","1","R169"
"RC0603FR-071K5L","1.5k","Resistor_SMD:R_0603_1608Metric_Pad0.98x0.95mm_HandSolder","1","R89"
"RC0603FR-072K2L","2.2k","Resistor_SMD:R_0603_1608Metric_Pad0.98x0.95mm_HandSolder","2","R144,R145"
"RC0603FR-072R2L","2.2","Resistor_SMD:R_0603_1608Metric_Pad0.98x0.95mm_HandSolder","7","R14,R15,R32,R33,R49,R67,R85"
"RC0603FR-073K9L","3.9k","Resistor_SMD:R_0603_1608Metric_Pad0.98x0.95mm_HandSolder","1","R134"
"RC0603FR-074K3L","4.3k","Resistor_SMD:R_0603_1608Metric_Pad0.98x0.95mm_HandSolder","1","R7"
"RC0603FR-074K7L","4.7k","Resistor_SMD:R_0603_1608Metric_Pad0.98x0.95mm_HandSolder","1","R71"
"RC0603FR-074K99L","4.99k","Resistor_SMD:R_0603_1608Metric_Pad0.98x0.95mm_HandSolder","1","R131"
"RC0603FR-075K1L","5.1k","Resistor_SMD:R_0603_1608Metric_Pad0.98x0.95mm_HandSolder","4","R18,R36,R149,R150"
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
